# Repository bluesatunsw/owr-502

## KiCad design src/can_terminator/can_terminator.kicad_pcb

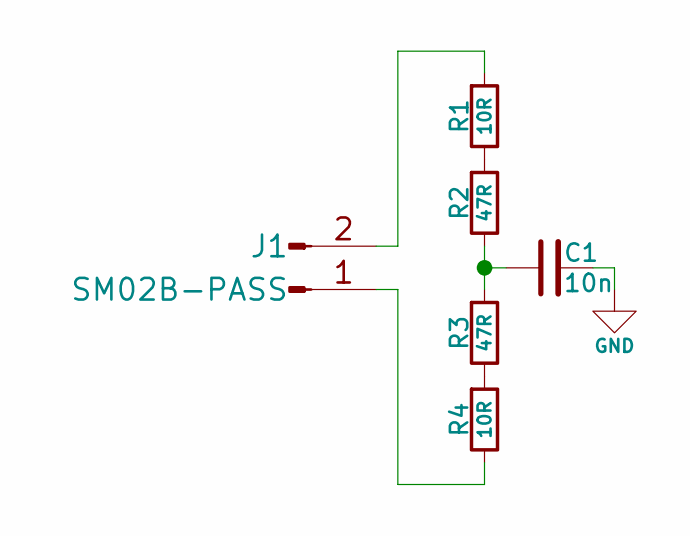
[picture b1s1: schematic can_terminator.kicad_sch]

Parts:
C1: 10n; C_0402_1005Metric
J1: SM02B-PASS
R1, R4: 10R; R_0402_1005Metric
R2, R3: 47R; R_0402_1005Metric

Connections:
GND: C1.2
unnamed: C1.1, R2.2, R3.1
unnamed: J1.1, R4.2
unnamed: J1.2, R1.1
unnamed: R1.2, R2.1
unnamed: R3.2, R4.1

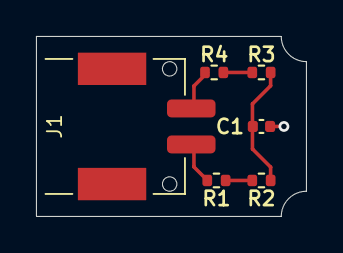
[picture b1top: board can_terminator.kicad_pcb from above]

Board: 2 copper layers, 15.0 x 10.0 mm, 6 parts (0 on the bottom side), 5 nets.

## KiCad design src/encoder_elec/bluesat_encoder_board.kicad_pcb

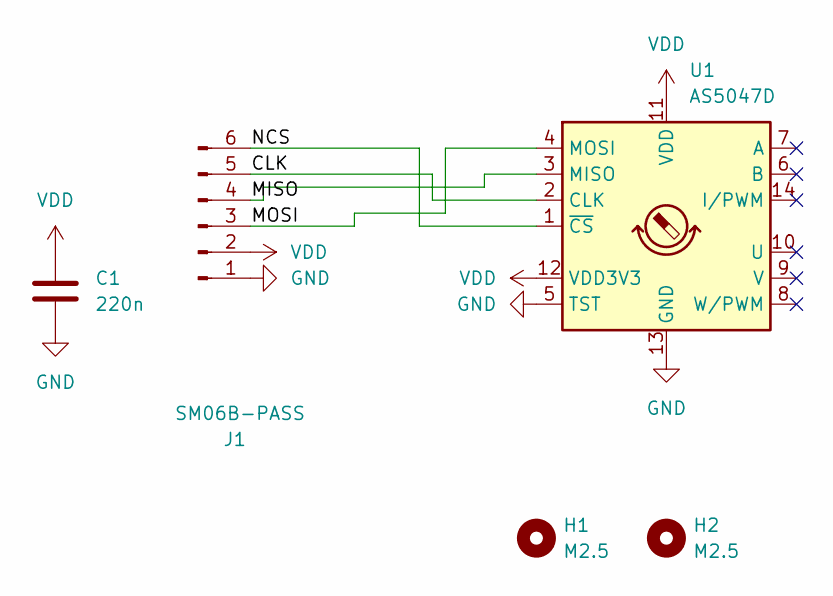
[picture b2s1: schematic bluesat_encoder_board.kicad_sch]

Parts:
C1: 220n; C_0402_1005Metric
H1, H2: M2.5
J1: SM06B-PASS
U1: AS5047D; TSSOP-14_4.4x5.0-0.65

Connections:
/CLK: J1.5, U1.2 (CLK)
/MISO: J1.4, U1.3 (MISO)
/MOSI: J1.3, U1.4 (MOSI)
/NCS: J1.6, U1.1 (~CS)
GND: C1.2, J1.1, U1.5 (TST), U1.13 (GND)
VDD: C1.1, J1.2, U1.11 (VDD), U1.12 (VDD3V3)

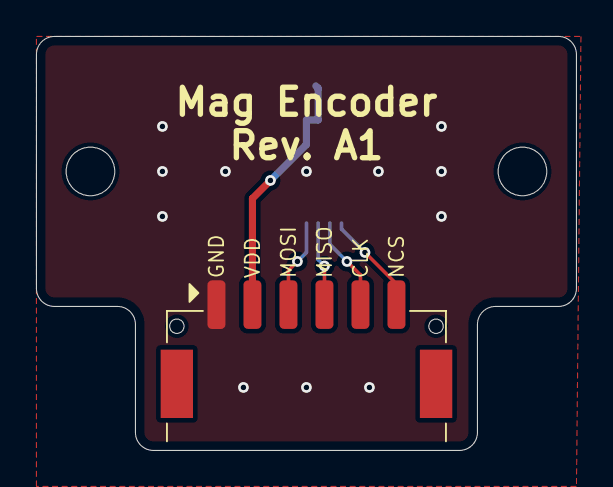
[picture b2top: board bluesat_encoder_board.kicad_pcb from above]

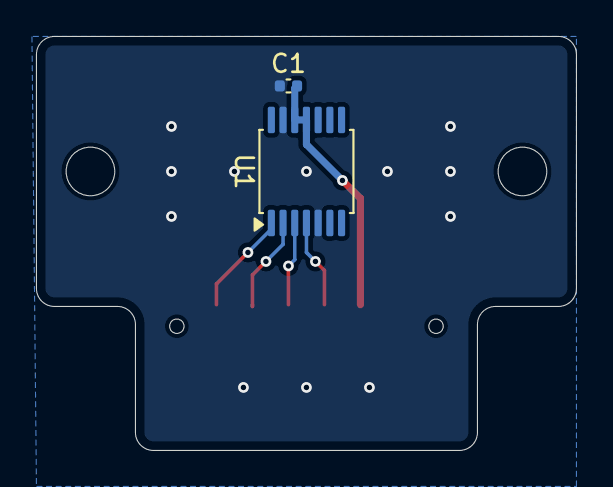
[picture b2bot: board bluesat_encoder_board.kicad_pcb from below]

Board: 2 copper layers, 30.0 x 23.0 mm, 5 parts (2 on the bottom side), 6 nets.

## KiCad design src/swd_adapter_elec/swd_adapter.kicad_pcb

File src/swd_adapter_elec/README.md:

# STLink Specification
STLINK-V3MINIE

## Purpose
Allows us to use Serial Wire Debug on our boards.
Don't have to do jank thing with the jumpers.

## Description
Should connect this board to our ribbon cables (see the 6 pin IPC on the main board spec).

Can't easily be done with just a connector - ribbon cables aren't exactly easy to crimp.

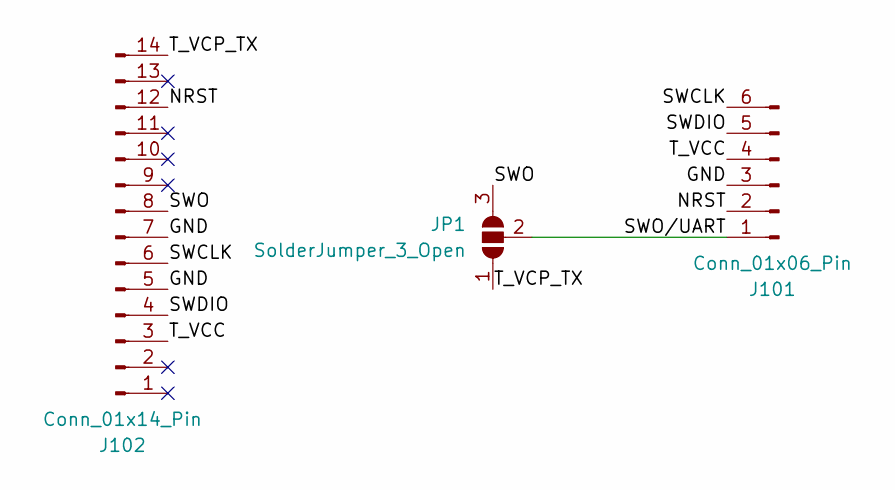
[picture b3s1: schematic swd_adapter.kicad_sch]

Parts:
J101: Conn_01x06_Pin; IDC6
J102: Conn_01x14_Pin; IDC14-Plug-Flipped
JP1: SolderJumper_3_Open; SolderJumper-3_P1.3mm_Open_RoundedPad1.0x1.5mm

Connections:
/GND: J101.3, J102.5, J102.7
/NRST: J101.2, J102.12
/SWCLK: J101.6, J102.6
/SWDIO: J101.5, J102.4
/SWO: J102.8, JP1.3 (B)
/SWO/UART: J101.1, JP1.2 (C)
/T_VCC: J101.4, J102.3
/T_VCP_TX: J102.14, JP1.1 (A)

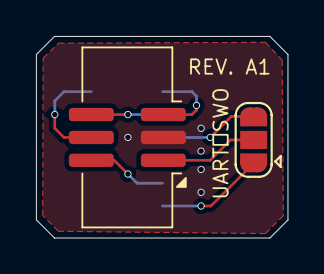
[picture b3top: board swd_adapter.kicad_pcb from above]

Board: 2 copper layers, 14.0 x 11.2 mm, 3 parts (1 on the bottom side), 8 nets.

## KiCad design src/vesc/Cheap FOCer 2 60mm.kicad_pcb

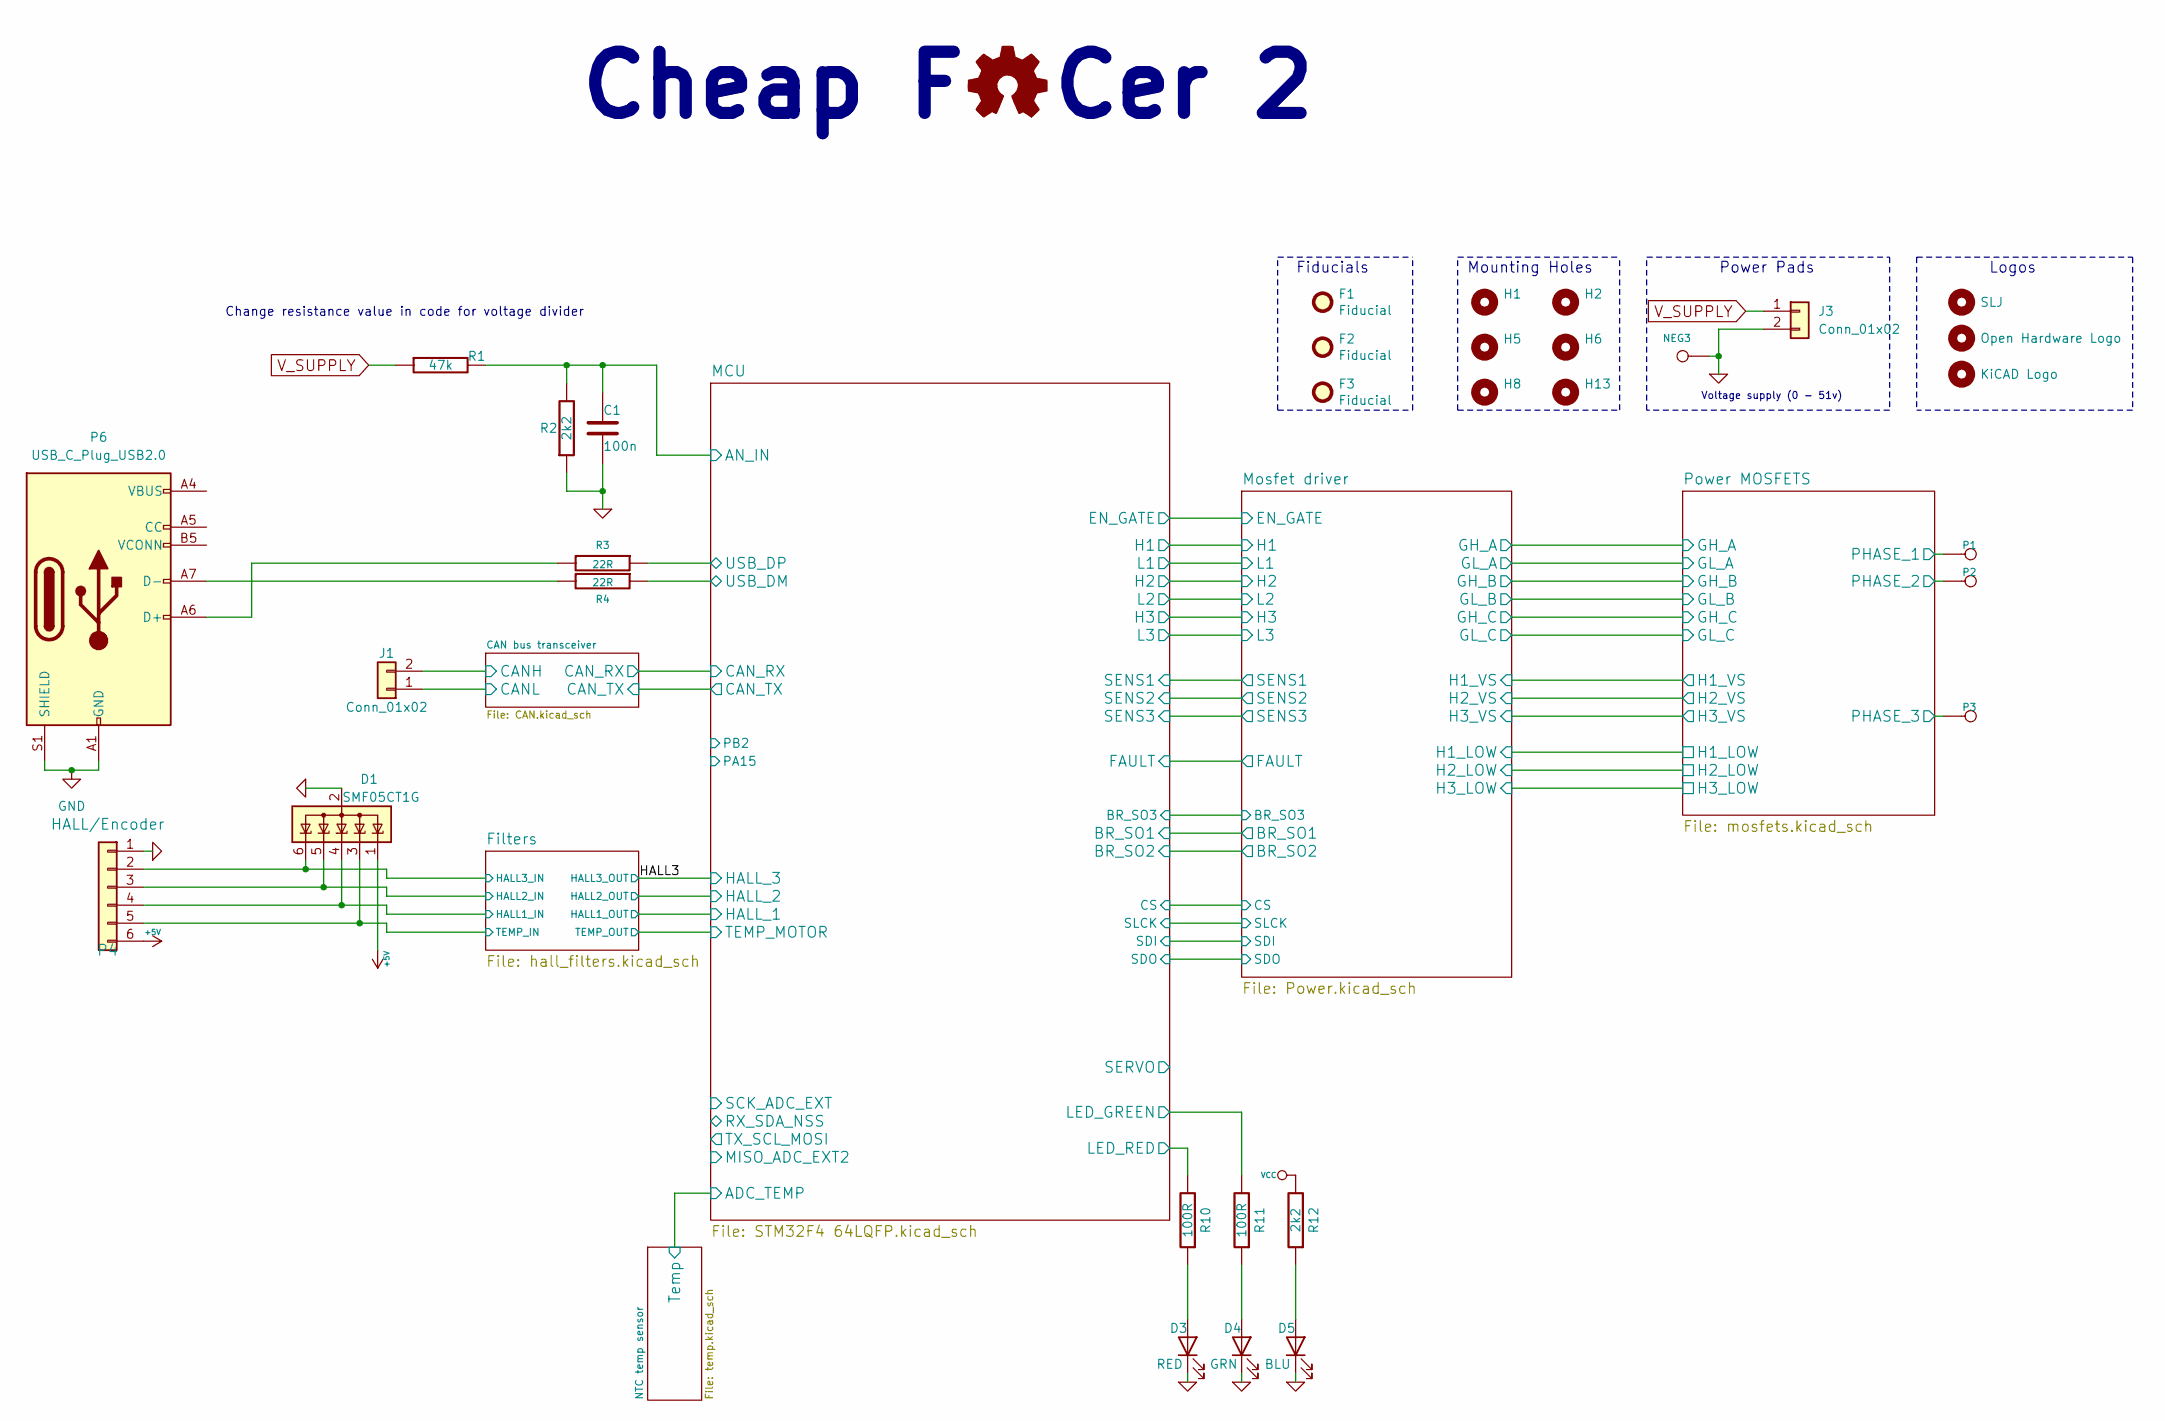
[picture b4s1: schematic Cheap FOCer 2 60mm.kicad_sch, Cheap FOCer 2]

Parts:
C1: 100n; C_0603_1608Metric
D1: SMF05CT1G; SOT-363_SC-70-6
D3: RED; LED_0603_1608Metric
D4: GRN; LED_0603_1608Metric
D5: BLU; LED_0603_1608Metric
F1, F2, F3: Fiducial; Fiducial_1mm_Dia_2mm_Outer
H1, H2, H5, H6, H8, H13: MountingHole; MountingHole_3.2mm_M3_ISO14580_Pad
H3: SLJ; Sam_J
H4: Open Hardware Logo; OSHW-Logo2_9.8x8mm_SilkScreen
H9: KiCAD Logo; KiCad-Logo2_5mm_SilkScreen
J1: Conn_01x02; JST_PH_B2B-PH-K_1x02_P2.00mm_Vertical
J3: Conn_01x02
NEG3: MOTOR3; 1pin_4mm
P1, P2, P3: MOTOR1; 1pin_4mm
P4: HALL/Encoder; JST_PH_B6B-PH-K_1x06_P2.00mm_Vertical
P6: USB_C_Plug_USB2.0
R1: 47k; R_0603_1608Metric
R2, R12: 2k2; R_0603_1608Metric
R3, R4: 22R; R_0603_1608Metric
R10, R11: 100R; R_0603_1608Metric

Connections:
/CAN bus transceiver/CANH: J1.2; also elsewhere on the board
/CAN bus transceiver/CANL: J1.1; also elsewhere on the board
/Filters/HALL1_IN: D1.4 (K), P4.4; also elsewhere on the board
/Filters/HALL2_IN: D1.3 (K), P4.5; also elsewhere on the board
/Filters/TEMP_IN: D1.5 (K), P4.3; also elsewhere on the board
/HALL3: D1.1 (K), P4.6; also elsewhere on the board
/MCU/AN_IN: C1.2, R1.2, R2.2; also elsewhere on the board
/MCU/LED_GREEN: R11.2; also elsewhere on the board
/MCU/LED_RED: R10.2; also elsewhere on the board
/MCU/USB_DM: R3.1; also elsewhere on the board
/MCU/USB_DP: R4.1; also elsewhere on the board
GND: C1.1, D1.2 (A), D3.1 (K), D4.1 (K), D5.1 (K), J3.2, NEG3.1, P4.1, P6.A1 (GND), P6.A12 (GND), P6.B1 (GND), P6.B12 (GND), P6.S1 (SHIELD), R2.1; also elsewhere on the board
unnamed: D3.2 (A), R10.1
unnamed: D4.2 (A), R11.1
unnamed: D5.2 (A), R12.1
unnamed 56: P6.A6 (D+), R3.2; also elsewhere on the board
unnamed 57: P6.A7 (D-), R4.2; also elsewhere on the board
unnamed: P6.A4 (VBUS), P6.A9 (VBUS), P6.B4 (VBUS), P6.B9 (VBUS)
VCC: D1.6 (K), P4.2, R12.2; also elsewhere on the board
V_SUPPLY: J3.1, R1.1; also elsewhere on the board

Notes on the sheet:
Power Pads
Mounting Holes
Logos
Cheap F Cer 2
Change resistance value in code for voltage divider
Voltage supply (0 - 51v)
Fiducials

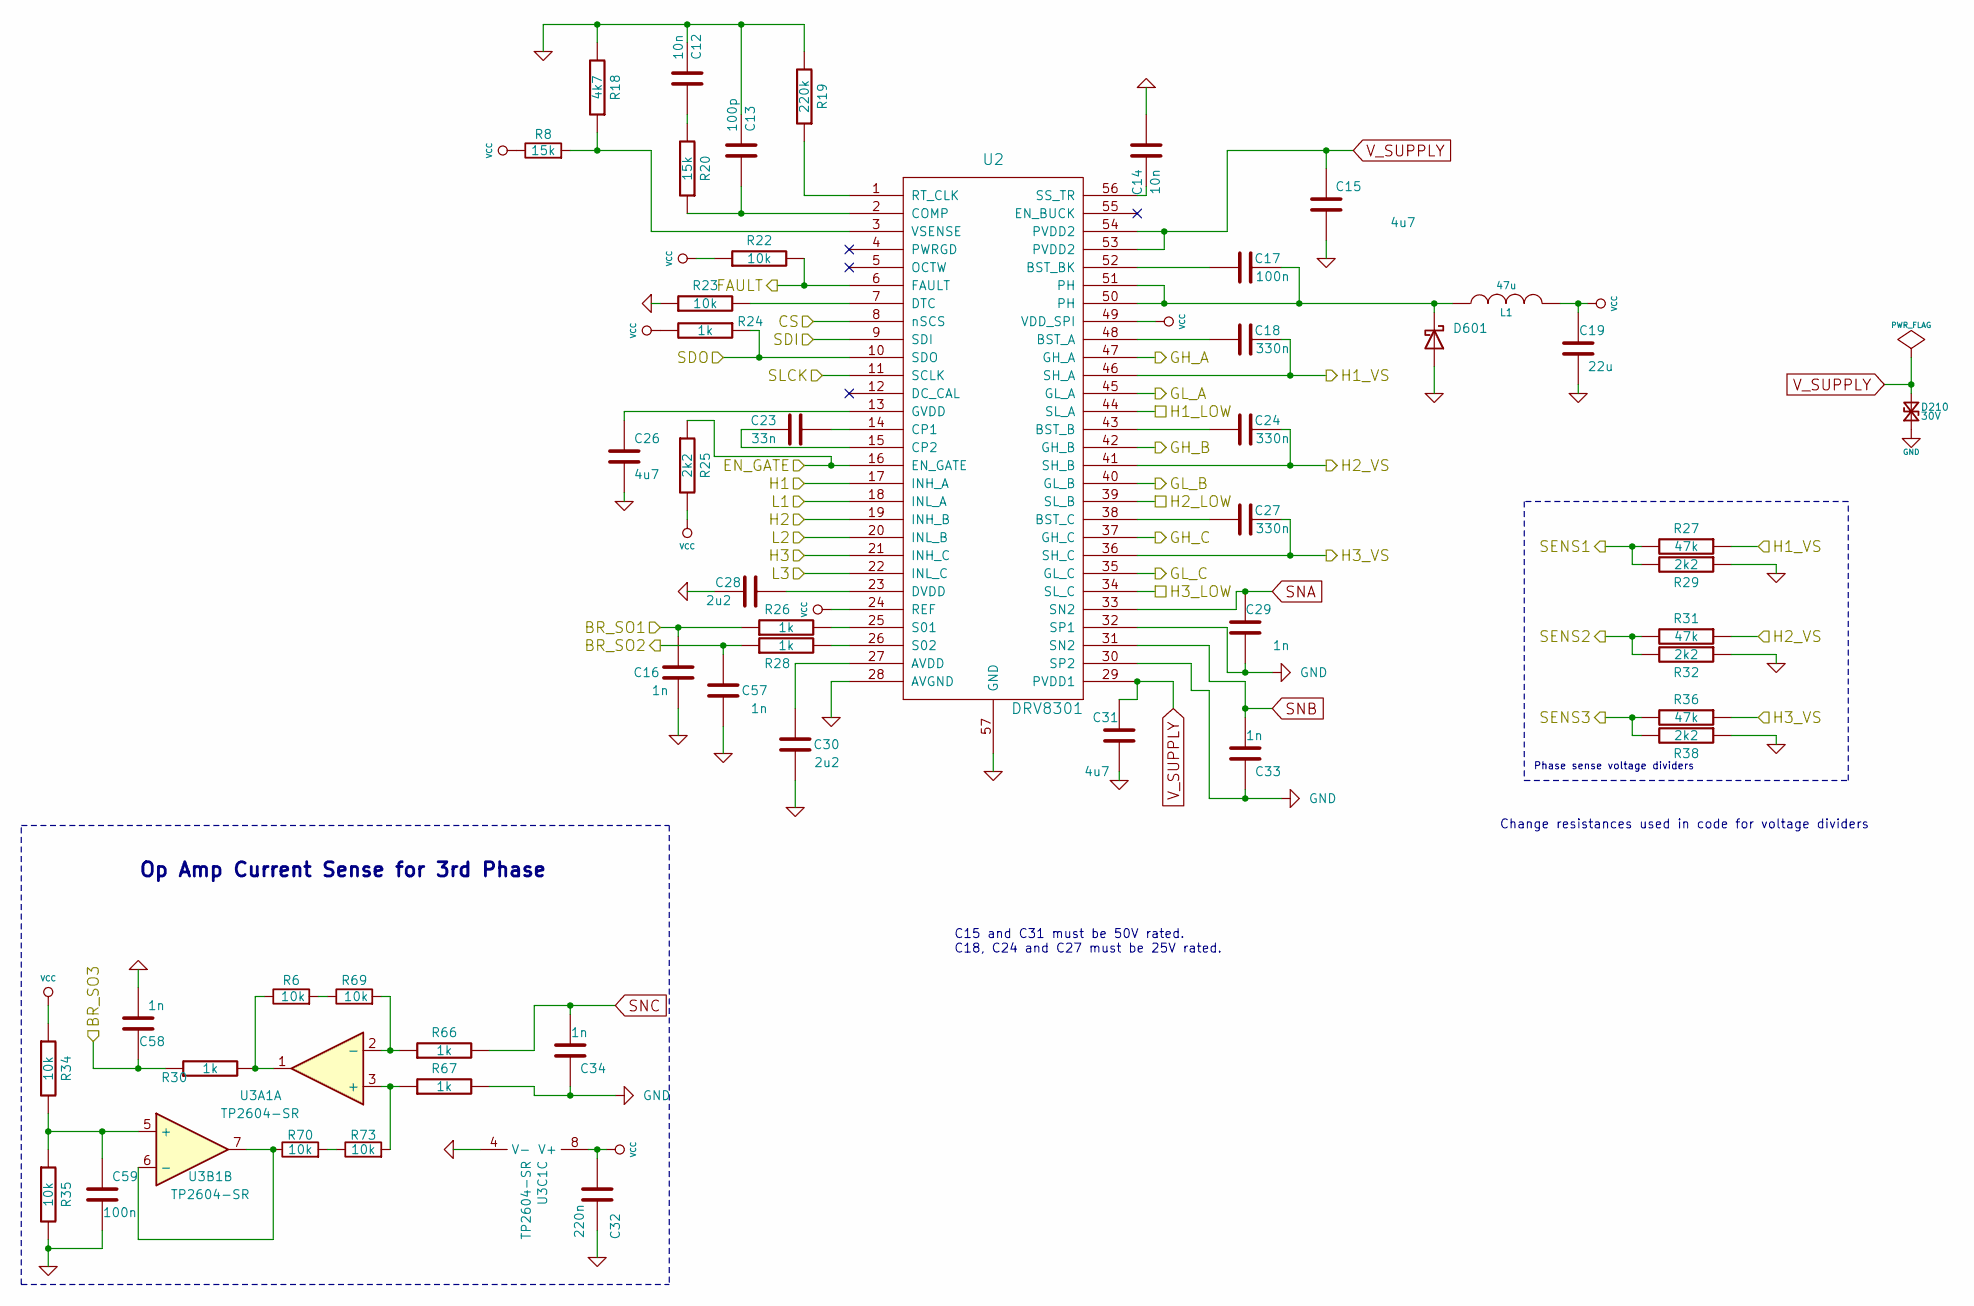
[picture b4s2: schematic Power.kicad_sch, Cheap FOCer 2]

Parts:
C12, C14: 10n; C_0402_1005Metric
C13: 100p; C_0402_1005Metric
C15, C26, C31: 4u7; C_1210_3225Metric
C16, C29, C33, C34, C57, C58: 1n; C_0402_1005Metric
C17: 100n; C_0603_1608Metric
C18, C24, C27: 330n; C_0603_1608Metric
C19: 22u; C_1210_3225Metric
C23: 33n; C_0603_1608Metric
C28: 2u2; C_1206_3216Metric
C30: 2u2; C_0603_1608Metric
C32: 220n; C_0402_1005Metric
C59: 100n; C_0402_1005Metric
D210: 30V; D_SMF
D601: D_Schottky; D_SOD-123
L1: 47u; L_Changjiang_FXL0630
R6, R22, R23, R34, R35, R69, R70, R73: 10k; R_0402_1005Metric
R8, R20: 15k; R_0402_1005Metric
R18: 4k7; R_0402_1005Metric
R19: 220k; R_0402_1005Metric
R24, R26, R28, R30, R66, R67: 1k; R_0402_1005Metric
R25, R29, R32, R38: 2k2; R_0402_1005Metric
R27, R31, R36: 47k; R_0402_1005Metric
U2: DRV8301; HTSSOP-56-1EP_6.1x14mm_P0.5mm_EP3.61x6.35mm
U3A1, U3B1, U3C1: TP2604-SR; SOP-8_3.76x4.96mm_P1.27mm

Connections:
/MCU/BR_SO1: C16.2, R26.1; also elsewhere on the board
/MCU/BR_SO2: C57.2, R28.1; also elsewhere on the board
/MCU/BR_SO3: C58.2, R30.1; also elsewhere on the board
/MCU/CS: U2.8 (nSCS); also elsewhere on the board
/MCU/EN_GATE: R25.1, U2.16 (EN_GATE); also elsewhere on the board
/MCU/FAULT: R22.2, U2.6 (FAULT); also elsewhere on the board
/MCU/H1: U2.17 (INH_A); also elsewhere on the board
/MCU/H2: U2.19 (INH_B); also elsewhere on the board
/MCU/H3: U2.21 (INH_C); also elsewhere on the board
/MCU/L1: U2.18 (INL_A); also elsewhere on the board
/MCU/L2: U2.20 (INL_B); also elsewhere on the board
/MCU/L3: U2.22 (INL_C); also elsewhere on the board
/MCU/SDI: U2.9 (SDI); also elsewhere on the board
/MCU/SDO: R24.1, U2.10 (SDO); also elsewhere on the board
/MCU/SENS1: R27.2, R29.2; also elsewhere on the board
/MCU/SENS2: R31.2, R32.2; also elsewhere on the board
/MCU/SENS3: R36.2, R38.2; also elsewhere on the board
/MCU/SLCK: U2.11 (SCLK); also elsewhere on the board
/Mosfet driver/GH_A: U2.47 (GH_A); also elsewhere on the board
/Mosfet driver/GH_B: U2.42 (GH_B); also elsewhere on the board
/Mosfet driver/GH_C: U2.37 (GH_C); also elsewhere on the board
/Mosfet driver/GL_A: U2.45 (GL_A); also elsewhere on the board
/Mosfet driver/GL_B: U2.40 (GL_B); also elsewhere on the board
/Mosfet driver/GL_C: U2.35 (GL_C); also elsewhere on the board
/Mosfet driver/H1_VS: C18.2, R27.1, U2.46 (SH_A); also elsewhere on the board
/Mosfet driver/H2_VS: C24.2, R31.1, U2.41 (SH_B); also elsewhere on the board
/Mosfet driver/H3_VS: C27.2, R36.1, U2.36 (SH_C); also elsewhere on the board
GND: C12.1, C13.1, C14.2, C15.1, C16.1, C19.1, C26.2, C28.2, C29.1, C30.1, C31.1, C32.1, C33.2, C34.2, C57.1, C58.1, C59.2, D210.1 (A1), D601.2 (A), R18.2, R19.2, R23.1, R29.1, R32.1, R35.2, R38.1, R67.2, U2.28 (AVGND), U2.30 (SP2), U2.32 (SP1), U2.57 (GND), U3C1.4 (V-); also elsewhere on the board
unnamed: C12.2, R20.2
unnamed: C17.2, D601.1 (K), L1.1, U2.50 (PH), U2.51 (PH)
unnamed: R6.2, R69.1
unnamed: R6.1, R30.2, U3A1.1
unnamed: R70.2, R73.1
unnamed: C30.2, U2.27 (AVDD)
unnamed: C18.1, U2.48 (BST_A)
unnamed: C24.1, U2.43 (BST_B)
unnamed: C17.1, U2.52 (BST_BK)
unnamed: C27.1, U2.38 (BST_C)
unnamed: C13.2, R20.1, U2.2 (COMP)
unnamed: C23.2, U2.14 (CP1)
unnamed: C23.1, U2.15 (CP2)
unnamed: R23.2, U2.7 (DTC)
unnamed: C28.1, U2.23 (DVDD)
unnamed: C26.1, U2.13 (GVDD)
unnamed: R19.1, U2.1 (RT_CLK)
unnamed: R26.2, U2.25 (S01)
unnamed: R28.2, U2.26 (S02)
unnamed: C14.1, U2.56 (SS_TR)
unnamed: R8.2, R18.1, U2.3 (VSENSE)
unnamed: R67.1, R73.2, U3A1.3 (+)
unnamed: R66.1, R69.2, U3A1.2 (-)
unnamed: C59.1, R34.2, R35.1, U3B1.5 (+)
unnamed: R70.1, U3B1.6 (-), U3B1.7
SNA: C29.2, U2.33 (SN2), U2.44 (SL_A); also elsewhere on the board
SNB: C33.1, U2.31 (SN2), U2.39 (SL_B); also elsewhere on the board
SNC: C34.1, R66.2, U2.34 (SL_C); also elsewhere on the board
VCC: C19.2, C32.2, L1.2, R8.1, R22.1, R24.2, R25.2, R34.1, U2.24 (REF), U2.49 (VDD_SPI), U3C1.8 (V+); also elsewhere on the board
V_SUPPLY: C15.2, C31.2, D210.2 (A2), U2.29 (PVDD1), U2.53 (PVDD2), U2.54 (PVDD2); also elsewhere on the board

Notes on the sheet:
C15 and C31 must be 50V rated. C18, C24 and C27 must be 25V rated.
Op Amp Current Sense for 3rd Phase
Change resistances used in code for voltage dividers
Phase sense voltage dividers

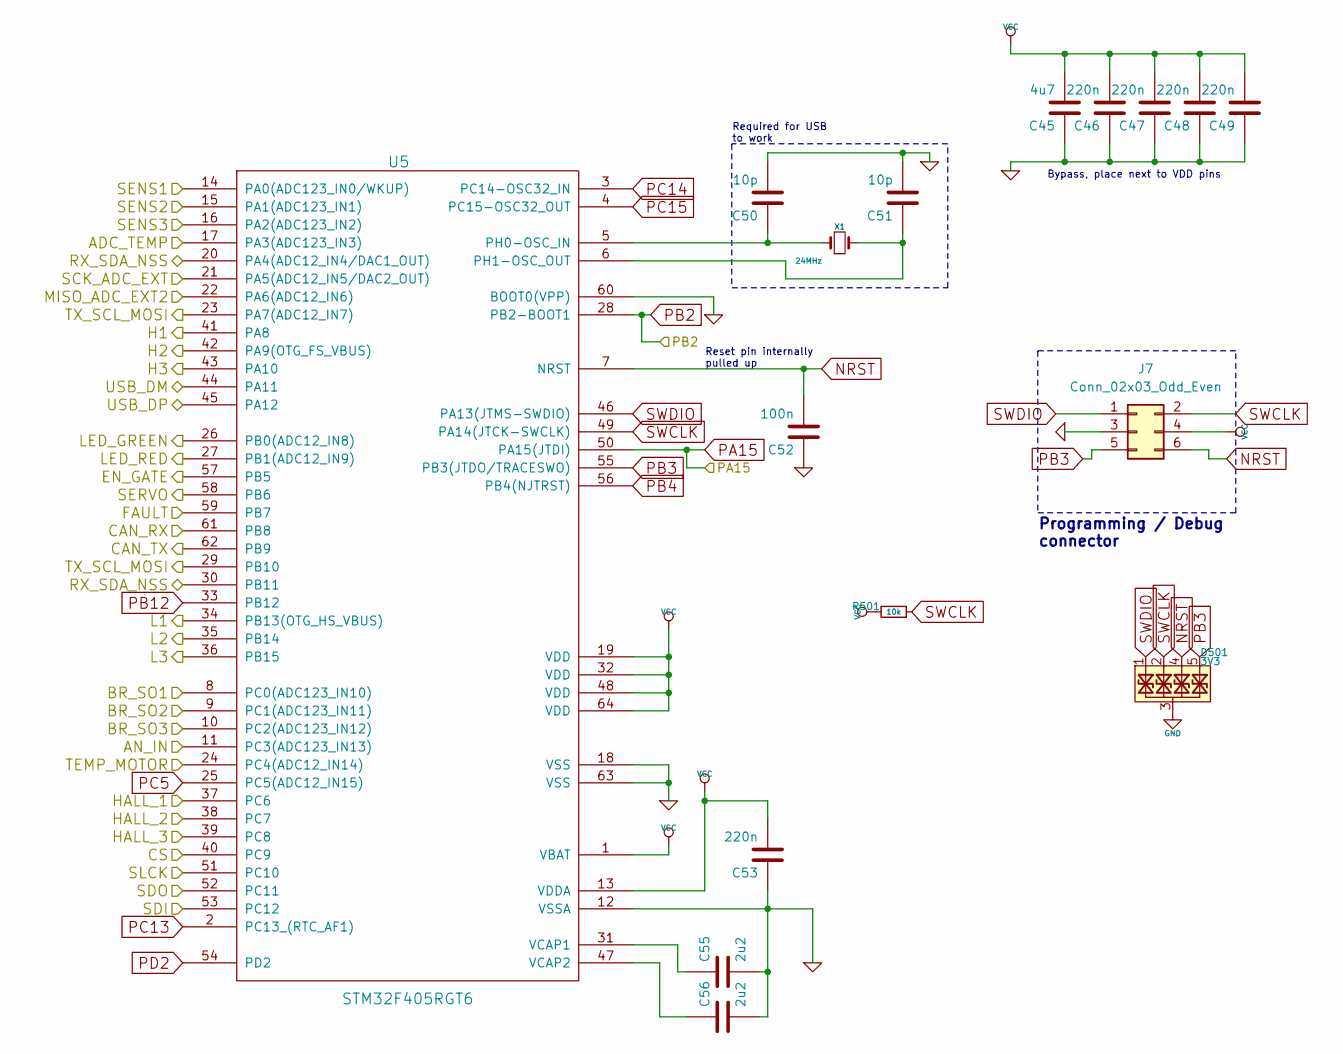
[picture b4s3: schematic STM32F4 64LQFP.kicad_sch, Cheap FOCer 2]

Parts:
C45: 4u7; C_0805_2012Metric
C46, C47, C48, C49, C53: 220n; C_0402_1005Metric
C50, C51: 10p; C_0402_1005Metric
C52: 100n; C_0402_1005Metric
C55, C56: 2u2; C_0603_1608Metric
D501: 3V3; Diodes_UDFN-10_1.0x2.5mm_P0.5mm
J7: Conn_02x03_Odd_Even; PinHeader_2x03_P1.27mm_Vertical_SMD
R501: 10k; R_0402_1005Metric
U5: STM32F405RGT6; lqfp64_pad_mod
X1: 24MHz; Crystal_SMD_2016-4Pin_2.0x1.6mm; mfg# ABM3B-8.0-10-1UT

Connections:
/CAN bus transceiver/CAN_RX: U5.61 (PB8); also elsewhere on the board
/CAN bus transceiver/CAN_TX: U5.62 (PB9); also elsewhere on the board
/Filters/HALL1_IN: U5.37 (PC6); also elsewhere on the board
/Filters/HALL2_IN: U5.38 (PC7); also elsewhere on the board
/Filters/TEMP_IN: U5.24 (PC4(ADC12_IN14)); also elsewhere on the board
/HALL3: U5.39 (PC8); also elsewhere on the board
/MCU/ADC_TEMP: U5.17 (PA3(ADC123_IN3)); also elsewhere on the board
/MCU/AN_IN: U5.11 (PC3(ADC123_IN13)); also elsewhere on the board
/MCU/BR_SO1: U5.8 (PC0(ADC123_IN10)); also elsewhere on the board
/MCU/BR_SO2: U5.9 (PC1(ADC123_IN11)); also elsewhere on the board
/MCU/BR_SO3: U5.10 (PC2(ADC123_IN12)); also elsewhere on the board
/MCU/CS: U5.40 (PC9); also elsewhere on the board
/MCU/EN_GATE: U5.57 (PB5); also elsewhere on the board
/MCU/FAULT: U5.59 (PB7); also elsewhere on the board
/MCU/H1: U5.41 (PA8); also elsewhere on the board
/MCU/H2: U5.42 (PA9(OTG_FS_VBUS)); also elsewhere on the board
/MCU/H3: U5.43 (PA10); also elsewhere on the board
/MCU/L1: U5.34 (PB13(OTG_HS_VBUS)); also elsewhere on the board
/MCU/L2: U5.35 (PB14); also elsewhere on the board
/MCU/L3: U5.36 (PB15); also elsewhere on the board
/MCU/LED_GREEN: U5.26 (PB0(ADC12_IN8)); also elsewhere on the board
/MCU/LED_RED: U5.27 (PB1(ADC12_IN9)); also elsewhere on the board
/MCU/MISO_ADC_EXT2: U5.22 (PA6(ADC12_IN6))
/MCU/RX_SDA_NSS: U5.20 (PA4(ADC12_IN4/DAC1_OUT)), U5.30 (PB11)
/MCU/SCK_ADC_EXT: U5.21 (PA5(ADC12_IN5/DAC2_OUT))
/MCU/SDI: U5.53 (PC12); also elsewhere on the board
/MCU/SDO: U5.52 (PC11); also elsewhere on the board
/MCU/SENS1: U5.14 (PA0(ADC123_IN0/WKUP)); also elsewhere on the board
/MCU/SENS2: U5.15 (PA1(ADC123_IN1)); also elsewhere on the board
/MCU/SENS3: U5.16 (PA2(ADC123_IN2)); also elsewhere on the board
/MCU/SERVO: U5.58 (PB6)
/MCU/SLCK: U5.51 (PC10); also elsewhere on the board
/MCU/TX_SCL_MOSI: U5.23 (PA7(ADC12_IN7)), U5.29 (PB10)
/MCU/USB_DM: U5.44 (PA11); also elsewhere on the board
/MCU/USB_DP: U5.45 (PA12); also elsewhere on the board
GND: C45.1, C46.1, C47.1, C48.1, C49.1, C50.2, C51.2, C52.1, C53.1, C55.2, C56.2, D501.3, D501.8, J7.3, U5.12 (VSSA), U5.18 (VSS), U5.60 (BOOT0(VPP)), U5.63 (VSS); also elsewhere on the board
NRST: C52.2, D501.4, D501.7, J7.6, U5.7 (NRST)
unnamed: C50.1, U5.5 (PH0-OSC_IN), X1.1
unnamed: C51.1, U5.6 (PH1-OSC_OUT), X1.2
unnamed: C55.1, U5.31 (VCAP1)
unnamed: C56.1, U5.47 (VCAP2)
PA15: U5.50 (PA15(JTDI))
PB2: U5.28 (PB2-BOOT1)
PB3: D501.5, D501.6, J7.5, U5.55 (PB3(JTDO/TRACESWO))
PB4: U5.56 (PB4(NJTRST))
PB12: U5.33 (PB12)
PC5: U5.25 (PC5(ADC12_IN15))
PC13: U5.2 (PC13_(RTC_AF1))
PC14: U5.3 (PC14-OSC32_IN)
PC15: U5.4 (PC15-OSC32_OUT)
PD2: U5.54 (PD2)
SWCLK: D501.2, D501.9, J7.2, R501.1, U5.49 (PA14(JTCK-SWCLK))
SWDIO: D501.1, D501.10, J7.1, U5.46 (PA13(JTMS-SWDIO))
VCC: C45.2, C46.2, C47.2, C48.2, C49.2, C53.2, J7.4, R501.2, U5.1 (VBAT), U5.13 (VDDA), U5.19 (VDD), U5.32 (VDD), U5.48 (VDD), U5.64 (VDD); also elsewhere on the board

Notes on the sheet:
Reset pin internally pulled up
Required for USB to work
Programming / Debug connector
Bypass, place next to VDD pins

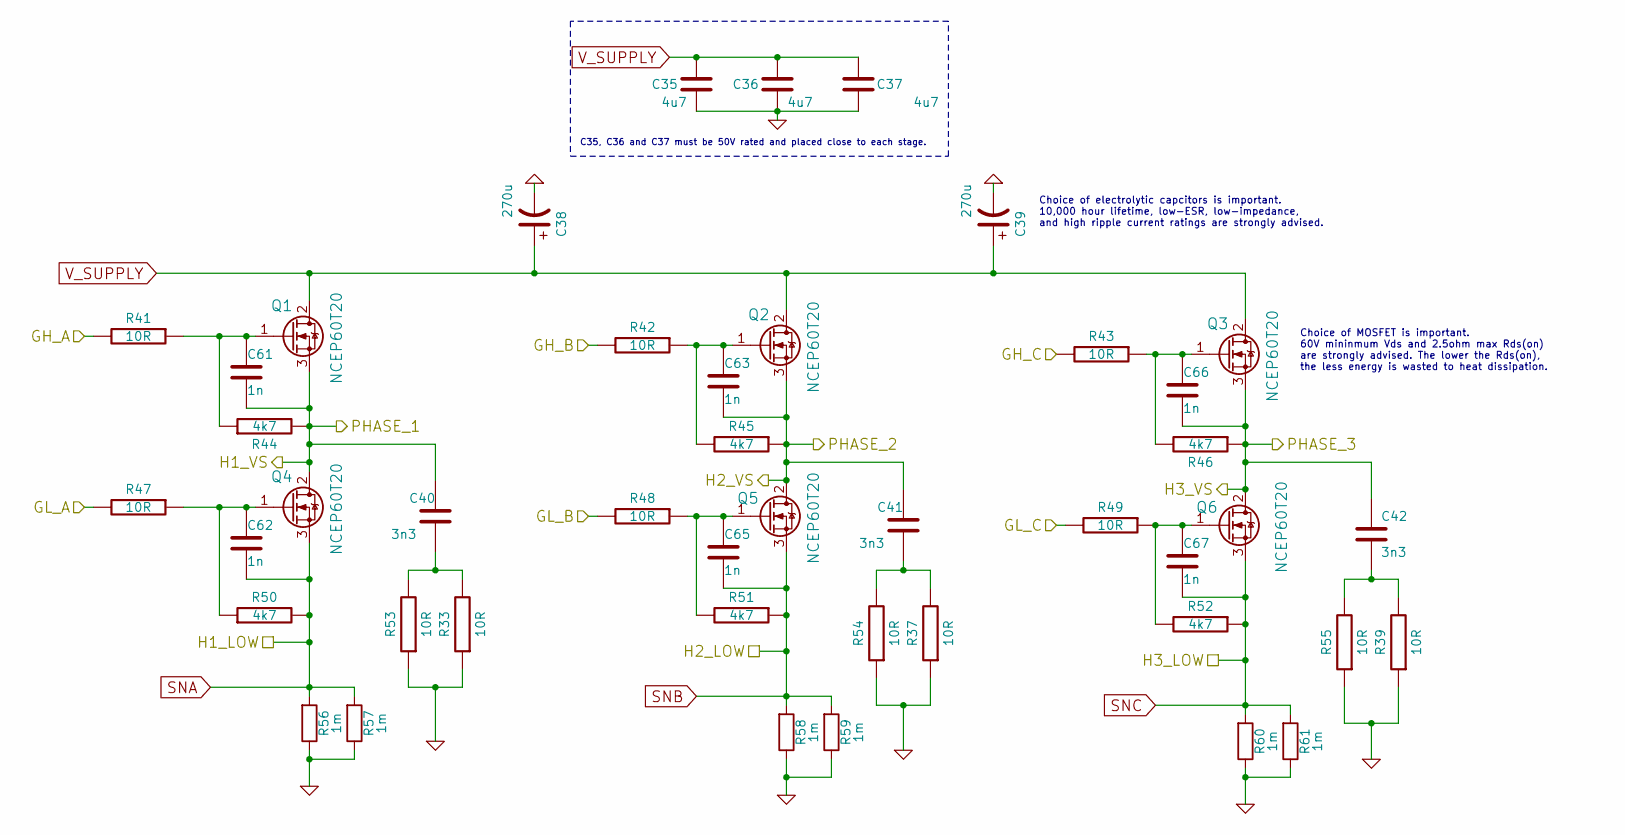
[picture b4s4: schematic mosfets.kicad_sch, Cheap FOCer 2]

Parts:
C35, C36, C37: 4u7; C_1210_3225Metric
C38, C39: 270u; CP_Elec_10x10
C40, C41, C42: 3n3; C_0402_1005Metric
C61, C62, C63, C65, C66, C67: 1n; C_0402_1005Metric
Q1, Q2, Q3, Q4, Q5, Q6: NCEP60T20; TO-220-3-heatsink-pad-tabdown
R33, R37, R39, R41, R42, R43, R47, R48, R49, R53, R54, R55: 10R; R_0402_1005Metric
R44, R45, R46, R50, R51, R52: 4k7; R_0402_1005Metric
R56, R57, R58, R59, R60, R61: 1m; R_2512_6332Metric

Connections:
/Mosfet driver/GH_A: R41.2; also elsewhere on the board
/Mosfet driver/GH_B: R42.2; also elsewhere on the board
/Mosfet driver/GH_C: R43.2; also elsewhere on the board
/Mosfet driver/GL_A: R47.2; also elsewhere on the board
/Mosfet driver/GL_B: R48.2; also elsewhere on the board
/Mosfet driver/GL_C: R49.2; also elsewhere on the board
/Mosfet driver/H1_VS: C40.1, C61.2, Q1.3 (S), Q4.2 (D), R44.2; also elsewhere on the board
/Mosfet driver/H2_VS: C41.1, C63.2, Q2.3 (S), Q5.2 (D), R45.1; also elsewhere on the board
/Mosfet driver/H3_VS: C42.1, C66.2, Q3.3 (S), Q6.2 (D), R46.1; also elsewhere on the board
GND: C35.1, C36.1, C37.1, C38.2, C39.2, R33.1, R37.1, R39.1, R53.1, R54.1, R55.1, R56.1, R57.1, R58.1, R59.1, R60.1, R61.1; also elsewhere on the board
unnamed: C40.2, R33.2, R53.2
unnamed: C41.2, R37.2, R54.2
unnamed: C42.2, R39.2, R55.2
unnamed: C61.1, Q1.1 (G), R41.1, R44.1
unnamed: C63.1, Q2.1 (G), R42.1, R45.2
unnamed: C66.1, Q3.1 (G), R43.1, R46.2
unnamed: C62.1, Q4.1 (G), R47.1, R50.1
unnamed: C65.1, Q5.1 (G), R48.1, R51.2
unnamed: C67.1, Q6.1 (G), R49.1, R52.2
SNA: C62.2, Q4.3 (S), R50.2, R56.2, R57.2; also elsewhere on the board
SNB: C65.2, Q5.3 (S), R51.1, R58.2, R59.2; also elsewhere on the board
SNC: C67.2, Q6.3 (S), R52.1, R60.2, R61.2; also elsewhere on the board
V_SUPPLY: C35.2, C36.2, C37.2, C38.1, C39.1, Q1.2 (D), Q2.2 (D), Q3.2 (D); also elsewhere on the board

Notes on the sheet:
Choice of MOSFET is important. 60V mininmum Vds and 2.5ohm max Rds(on) are strongly advised. The lower the Rds(on), the less energy is wasted to heat dissipation.
C35, C36 and C37 must be 50V rated and placed close to each stage.
Choice of electrolytic capcitors is important. 10,000 hour lifetime, low-ESR, low-impedance, and high ripple current ratings are strongly advised.

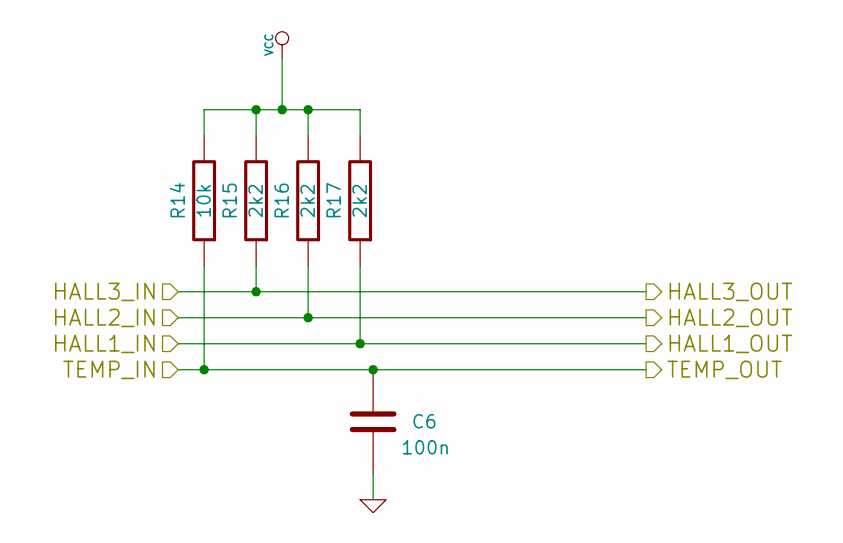
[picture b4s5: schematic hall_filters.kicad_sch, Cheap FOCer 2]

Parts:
C6: 100n
R14: 10k
R15, R16, R17: 2k2

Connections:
/Filters/HALL1_IN: R17.1; also elsewhere on the board
/Filters/HALL2_IN: R16.1; also elsewhere on the board
/Filters/TEMP_IN: C6.2, R14.1; also elsewhere on the board
/HALL3: R15.1; also elsewhere on the board
GND: C6.1; also elsewhere on the board
VCC: R14.2, R15.2, R16.2, R17.2; also elsewhere on the board

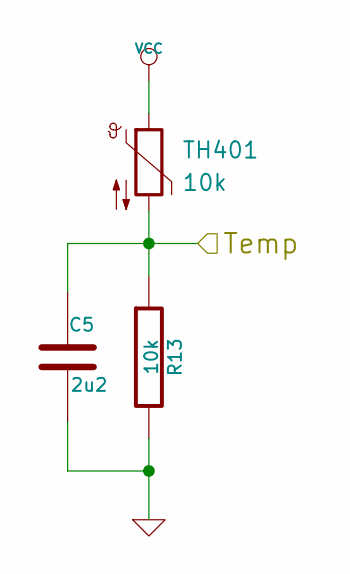
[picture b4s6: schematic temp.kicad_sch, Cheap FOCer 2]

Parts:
C5: 2u2; C_1206_3216Metric
R13: 10k; R_0402_1005Metric
TH401: 10k; R_0402_1005Metric

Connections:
/MCU/ADC_TEMP: C5.1, R13.1, TH401.2; also elsewhere on the board
GND: C5.2, R13.2; also elsewhere on the board
VCC: TH401.1; also elsewhere on the board

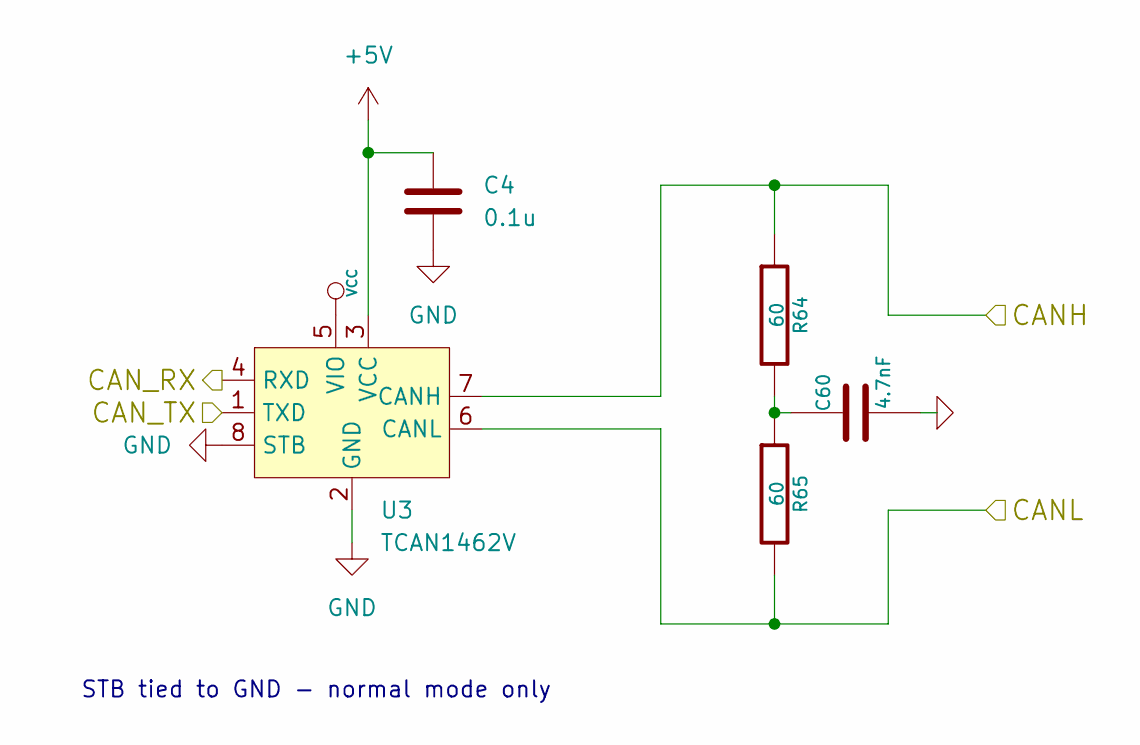
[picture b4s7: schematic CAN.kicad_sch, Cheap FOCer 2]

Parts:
C4: 0.1u
C60: 4.7nF; C_0603_1608Metric
R64, R65: 60; R_0603_1608Metric
U3: TCAN1462V

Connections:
/CAN bus transceiver/CANH: R64.1, U3.7 (CANH); also elsewhere on the board
/CAN bus transceiver/CANL: R65.2, U3.6 (CANL); also elsewhere on the board
/CAN bus transceiver/CAN_RX: U3.4 (RXD); also elsewhere on the board
/CAN bus transceiver/CAN_TX: U3.1 (TXD); also elsewhere on the board
GND: C4.2, C60.2, U3.2 (GND), U3.8 (STB), U3.9 (EP); also elsewhere on the board
unnamed: C60.1, R64.2, R65.1
unnamed 71: C4.1, U3.3 (VCC); also elsewhere on the board
VCC: U3.5 (VIO); also elsewhere on the board

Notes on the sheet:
STB tied to GND - normal mode only
